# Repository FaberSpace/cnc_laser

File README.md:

# cnc_laser
Laser driver for cnc

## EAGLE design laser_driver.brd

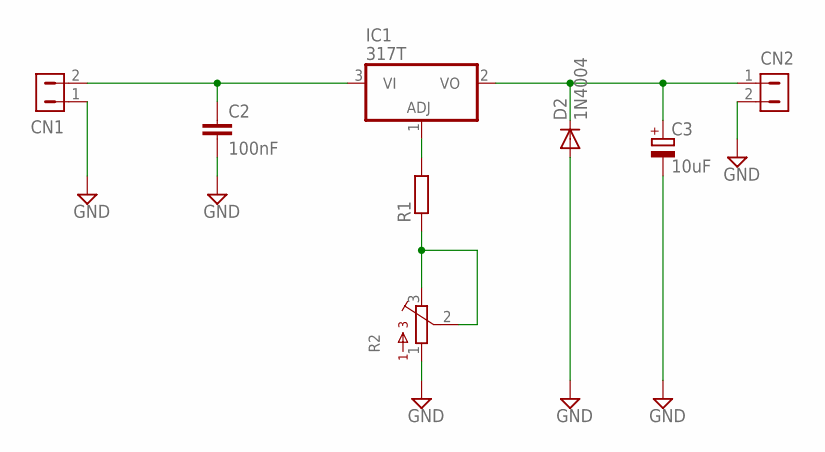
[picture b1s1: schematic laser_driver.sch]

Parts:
C2: 100nF; C2.5-3
C3: 10uF; E2-5
CN1, CN2: HDR-1X2-SIP-100; SIP-100-2V
D2: 1N4004; DO41-10
IC1: 317T; TO220H
R1: R0204/7; 0204/7
R2: 3386-F; 3386F

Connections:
GND: C2.2, C3.-, CN1.1, CN2.2, D2.A, R2.1
unnamed: C2.1, CN1.2, IC1.3 (VI)
unnamed: IC1.1 (ADJ), R1.2
unnamed: R1.1, R2.2, R2.3
unnamed: C3.+, CN2.1, D2.C, IC1.2 (VO)

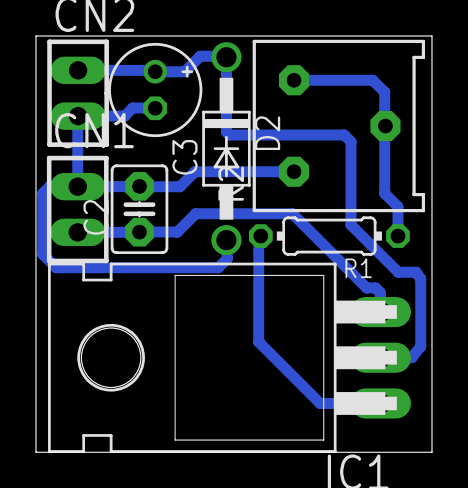
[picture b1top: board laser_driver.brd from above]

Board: 2 copper layers, 22.0 x 23.1 mm, 8 parts (0 on the bottom side), 5 nets.

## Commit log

2015-10-07 added laser driver for cnc
    added laser driver for cnc
2015-10-07 Create README.md
    Laser driver for cnc

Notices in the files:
parts and their libraries:
con-hdrs40: Copyright (C) 2004, Bob Starr (bobstarr@mindspring.com)
